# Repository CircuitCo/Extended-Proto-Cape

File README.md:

Extended-Proto-Cape
===================

The Extended Proto Cape provides more prototyping area for the BeagleBone Black. Users can still have access to the extra areas on each side of the BeagleBone Black's expansion headers even when another cape is stacked. Signals from the expansion headers are also broken out to edges of the PCB.

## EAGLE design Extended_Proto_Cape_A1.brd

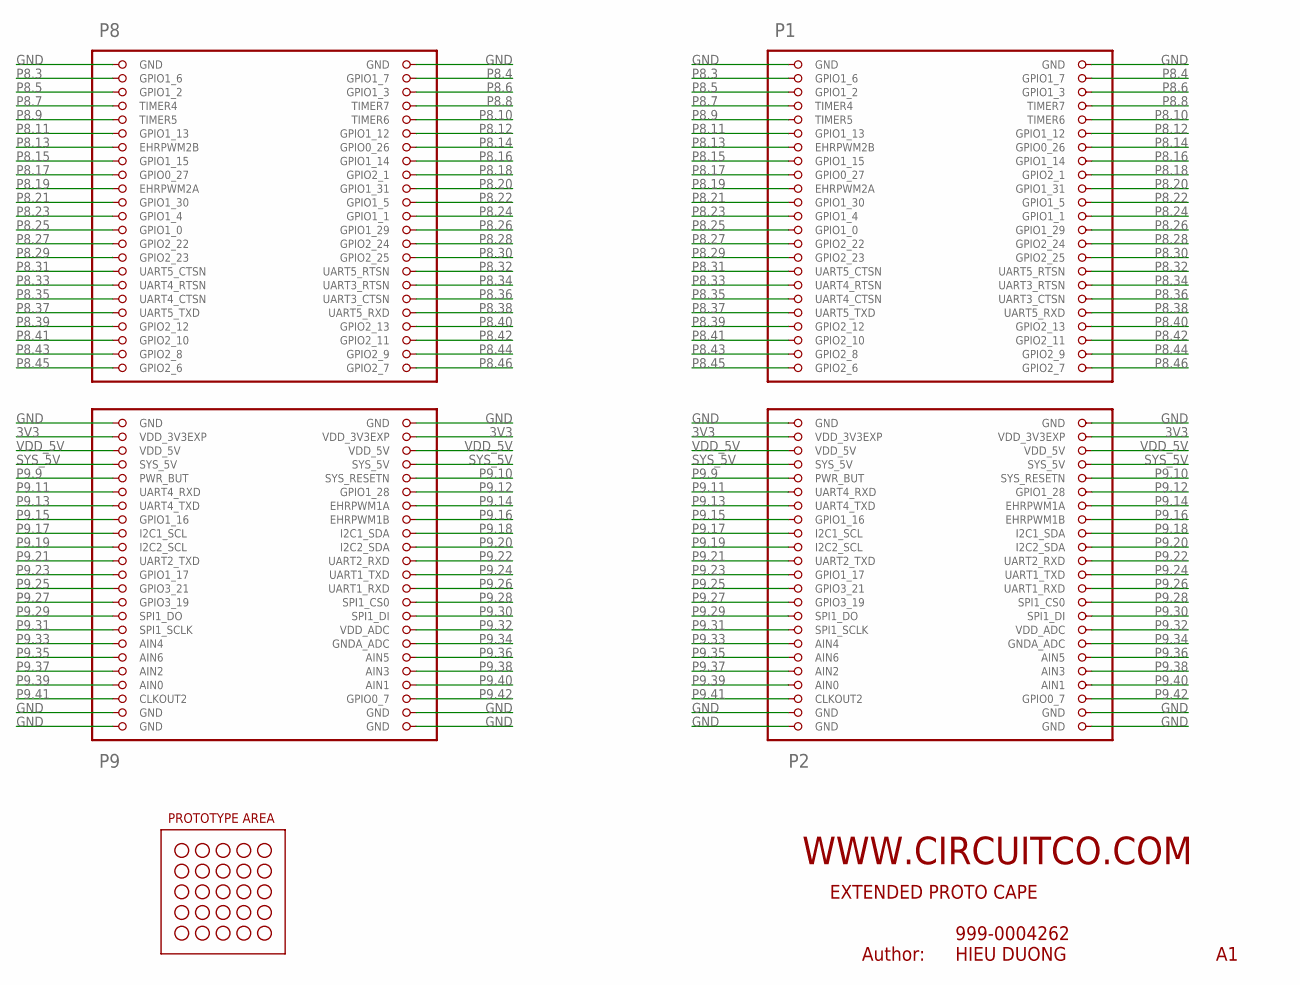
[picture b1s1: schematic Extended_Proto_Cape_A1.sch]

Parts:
U1: BB_OL_EXTPROTO
U2: PROTO_CAPE_EXT
U$2: PROTOTYPE_AREA_EXT

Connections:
3V3: U1.49 (VDD_3V3EXP), U1.50 (VDD_3V3EXP), U2.49 (VDD_3V3EXP), U2.50 (VDD_3V3EXP)
GND: U1.1 (GND), U1.2 (GND), U1.47 (GND), U1.48 (GND), U1.89 (GND), U1.90 (GND), U1.91 (GND), U1.92 (GND), U2.1 (GND), U2.2 (GND), U2.47 (GND), U2.48 (GND), U2.89 (GND), U2.90 (GND), U2.91 (GND), U2.92 (GND)
P8.3: U1.3 (GPIO1_6), U2.3 (GPIO1_6)
P8.4: U1.4 (GPIO1_7), U2.4 (GPIO1_7)
P8.5: U1.5 (GPIO1_2), U2.5 (GPIO1_2)
P8.6: U1.6 (GPIO1_3), U2.6 (GPIO1_3)
P8.7: U1.7 (TIMER4), U2.7 (TIMER4)
P8.8: U1.8 (TIMER7), U2.8 (TIMER7)
P8.9: U1.9 (TIMER5), U2.9 (TIMER5)
P8.10: U1.10 (TIMER6), U2.10 (TIMER6)
P8.11: U1.11 (GPIO1_13), U2.11 (GPIO1_13)
P8.12: U1.12 (GPIO1_12), U2.12 (GPIO1_12)
P8.13: U1.13 (EHRPWM2B), U2.13 (EHRPWM2B)
P8.14: U1.14 (GPIO0_26), U2.14 (GPIO0_26)
P8.15: U1.15 (GPIO1_15), U2.15 (GPIO1_15)
P8.16: U1.16 (GPIO1_14), U2.16 (GPIO1_14)
P8.17: U1.17 (GPIO0_27), U2.17 (GPIO0_27)
P8.18: U1.18 (GPIO2_1), U2.18 (GPIO2_1)
P8.19: U1.19 (EHRPWM2A), U2.19 (EHRPWM2A)
P8.20: U1.20 (GPIO1_31), U2.20 (GPIO1_31)
P8.21: U1.21 (GPIO1_30), U2.21 (GPIO1_30)
P8.22: U1.22 (GPIO1_5), U2.22 (GPIO1_5)
P8.23: U1.23 (GPIO1_4), U2.23 (GPIO1_4)
P8.24: U1.24 (GPIO1_1), U2.24 (GPIO1_1)
P8.25: U1.25 (GPIO1_0), U2.25 (GPIO1_0)
P8.26: U1.26 (GPIO1_29), U2.26 (GPIO1_29)
P8.27: U1.27 (GPIO2_22), U2.27 (GPIO2_22)
P8.28: U1.28 (GPIO2_24), U2.28 (GPIO2_24)
P8.29: U1.29 (GPIO2_23), U2.29 (GPIO2_23)
P8.30: U1.30 (GPIO2_25), U2.30 (GPIO2_25)
P8.31: U1.31 (UART5_CTSN), U2.31 (UART5_CTSN)
P8.32: U1.32 (UART5_RTSN), U2.32 (UART5_RTSN)
P8.33: U1.33 (UART4_RTSN), U2.33 (UART4_RTSN)
P8.34: U1.34 (UART3_RTSN), U2.34 (UART3_RTSN)
P8.35: U1.35 (UART4_CTSN), U2.35 (UART4_CTSN)
P8.36: U1.36 (UART3_CTSN), U2.36 (UART3_CTSN)
P8.37: U1.37 (UART5_TXD), U2.37 (UART5_TXD)
P8.38: U1.38 (UART5_RXD), U2.38 (UART5_RXD)
P8.39: U1.39 (GPIO2_12), U2.39 (GPIO2_12)
P8.40: U1.40 (GPIO2_13), U2.40 (GPIO2_13)
P8.41: U1.41 (GPIO2_10), U2.41 (GPIO2_10)
P8.42: U1.42 (GPIO2_11), U2.42 (GPIO2_11)
P8.43: U1.43 (GPIO2_8), U2.43 (GPIO2_8)
P8.44: U1.44 (GPIO2_9), U2.44 (GPIO2_9)
P8.45: U1.45 (GPIO2_6), U2.45 (GPIO2_6)
P8.46: U1.46 (GPIO2_7), U2.46 (GPIO2_7)
P9.9: U1.55 (PWR_BUT), U2.55 (PWR_BUT)
P9.10: U1.56 (SYS_RESETN), U2.56 (SYS_RESETN)
P9.11: U1.57 (UART4_RXD), U2.57 (UART4_RXD)
P9.12: U1.58 (GPIO1_28), U2.58 (GPIO1_28)
P9.13: U1.59 (UART4_TXD), U2.59 (UART4_TXD)
P9.14: U1.60 (EHRPWM1A), U2.60 (EHRPWM1A)
P9.15: U1.61 (GPIO1_16), U2.61 (GPIO1_16)
P9.16: U1.62 (EHRPWM1B), U2.62 (EHRPWM1B)
P9.17: U1.63 (I2C1_SCL), U2.63 (I2C1_SCL)
P9.18: U1.64 (I2C1_SDA), U2.64 (I2C1_SDA)
P9.19: U1.65 (I2C2_SCL), U2.65 (I2C2_SCL)
P9.20: U1.66 (I2C2_SDA), U2.66 (I2C2_SDA)
P9.21: U1.67 (UART2_TXD), U2.67 (UART2_TXD)
P9.22: U1.68 (UART2_RXD), U2.68 (UART2_RXD)
P9.23: U1.69 (GPIO1_17), U2.69 (GPIO1_17)
P9.24: U1.70 (UART1_TXD), U2.70 (UART1_TXD)
P9.25: U1.71 (GPIO3_21), U2.71 (GPIO3_21)
P9.26: U1.72 (UART1_RXD), U2.72 (UART1_RXD)
P9.27: U1.73 (GPIO3_19), U2.73 (GPIO3_19)
P9.28: U1.74 (SPI1_CS0), U2.74 (SPI1_CS0)
P9.29: U1.75 (SPI1_DO), U2.75 (SPI1_DO)
P9.30: U1.76 (SPI1_DI), U2.76 (SPI1_DI)
P9.31: U1.77 (SPI1_SCLK), U2.77 (SPI1_SCLK)
P9.32: U1.78 (VDD_ADC), U2.78 (VDD_ADC)
P9.33: U1.79 (AIN4), U2.79 (AIN4)
P9.34: U1.80 (GNDA_ADC), U2.80 (GNDA_ADC)
P9.35: U1.81 (AIN6), U2.81 (AIN6)
P9.36: U1.82 (AIN5), U2.82 (AIN5)
P9.37: U1.83 (AIN2), U2.83 (AIN2)
P9.38: U1.84 (AIN3), U2.84 (AIN3)
P9.39: U1.85 (AIN0), U2.85 (AIN0)
P9.40: U1.86 (AIN1), U2.86 (AIN1)
P9.41: U1.87 (CLKOUT2), U2.87 (CLKOUT2)
P9.42: U1.88 (GPIO0_7), U2.88 (GPIO0_7)
SYS_5V: U1.53 (SYS_5V), U1.54 (SYS_5V), U2.53 (SYS_5V), U2.54 (SYS_5V)
VDD_5V: U1.51 (VDD_5V), U1.52 (VDD_5V), U2.51 (VDD_5V), U2.52 (VDD_5V)

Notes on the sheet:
PROTOTYPE AREA
Author:

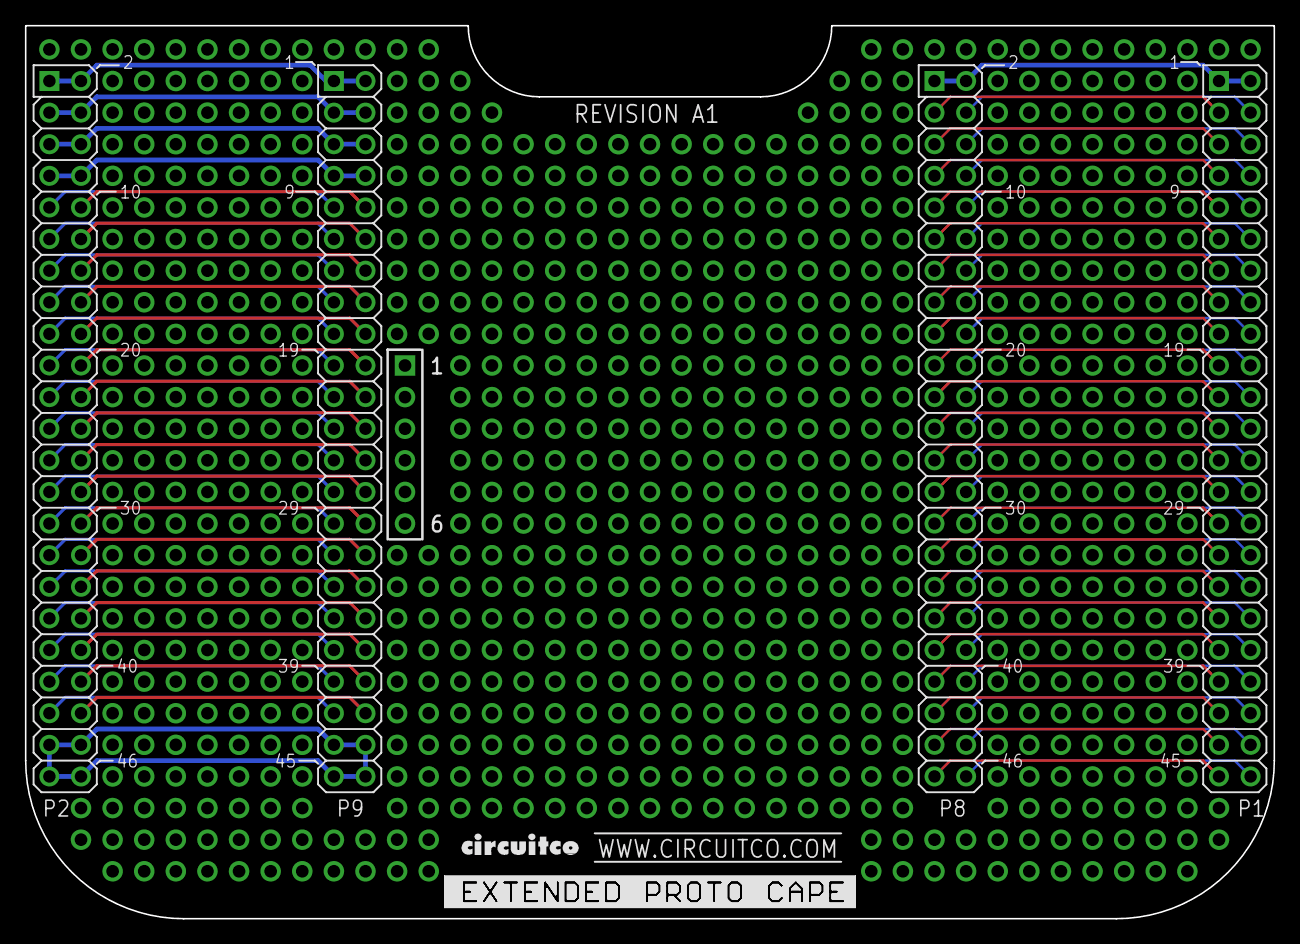
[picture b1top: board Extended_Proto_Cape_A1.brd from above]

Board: 2 copper layers, 100.3 x 71.8 mm, 5 parts (0 on the bottom side), 82 nets.

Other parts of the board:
DRILEGEND: DRILEGEND
U$1: NEGA-EXTPROTOCAPE

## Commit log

2014-03-20 add design files
